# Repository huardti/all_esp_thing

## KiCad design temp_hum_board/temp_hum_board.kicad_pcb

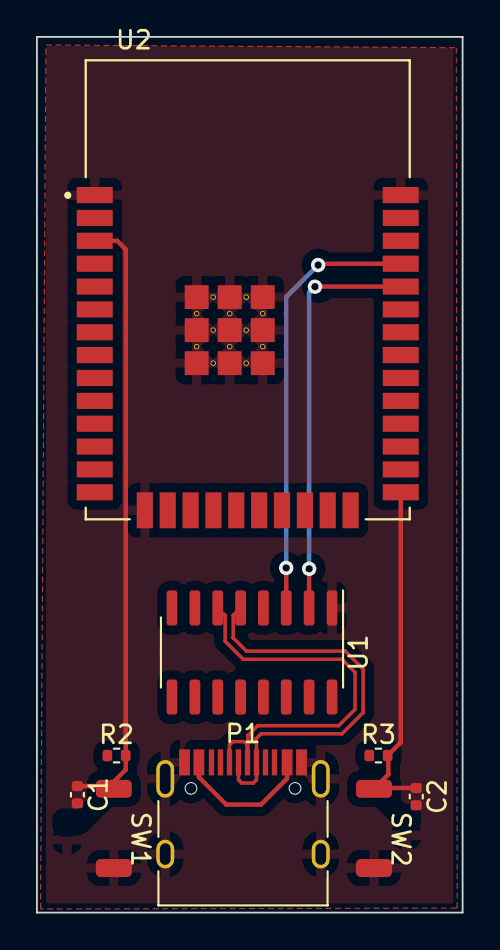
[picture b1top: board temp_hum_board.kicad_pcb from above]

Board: 2 copper layers, 23.6 x 48.7 mm, 9 parts (0 on the bottom side), 9 nets.

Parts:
C1, C2: 0,1µF; C_0402_1005Metric
P1: USB_C_Plug_USB2.0; USB_C_Receptacle_HRO_TYPE-C-31-M-12
R2, R3: 10K; R_0402_1005Metric
SW1, SW2: SW_Push; tactile switch
U1: CH340C; SOIC-16_3.9x9.9mm_P1.27mm
U2: ESP32-WROOM-32E_(4MB); MODULE_ESP32-WROOM-32E_(4MB)

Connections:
+3V3: R2.1, R3.1, U2.2 (3V3)
/D+: P1.A6 (D+), P1.B6 (D+), U1.5 (UD+)
/D-: P1.A7 (D-), P1.B7 (D-), U1.6 (UD-)
EN: C1.1, R2.2, SW1.1, U2.3 (EN)
GND: C1.2, C2.2, P1.A1 (GND), P1.A12 (GND), P1.B1 (GND), P1.B12 (GND), P1.S1 (SHIELD), SW1.2, SW2.2, U1.1 (GND), U2.1 (GND), U2.15 (GND), U2.38 (GND), U2.39_1 (GND), U2.39_2 (GND), U2.39_3 (GND), U2.39_4 (GND), U2.39_5 (GND), U2.39_6 (GND), U2.39_7 (GND), U2.39_8 (GND), U2.39_9 (GND), U2.39_10 (GND), U2.39_11 (GND), U2.39_12 (GND), U2.39_13 (GND), U2.39_14 (GND), U2.39_15 (GND), U2.39_16 (GND), U2.39_17 (GND), U2.39_18 (GND), U2.39_19 (GND), U2.39_20 (GND), U2.39_21 (GND)
IO0: C2.1, R3.2, SW2.1, U2.25 (IO0)
RXD0: U1.2 (TXD), U2.34 (RXD0)
TXD0: U1.3 (RXD), U2.35 (TXD0)
VPP: P1.A4 (VBUS), P1.A9 (VBUS), P1.B4 (VBUS), P1.B9 (VBUS)

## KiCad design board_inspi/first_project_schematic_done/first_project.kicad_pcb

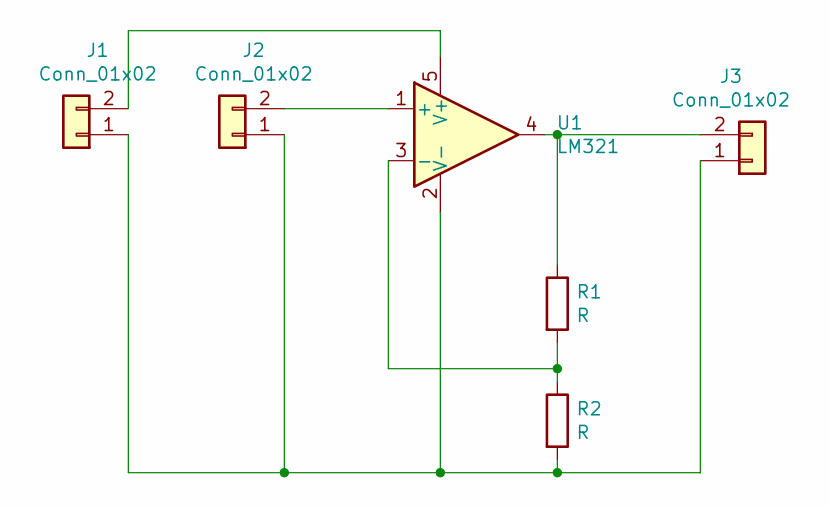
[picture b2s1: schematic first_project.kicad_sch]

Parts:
J1: Conn_01x02; JST_EH_B2B-EH-A_1x02_P2.50mm_Vertical
J2, J3: Conn_01x02; JST_PH_B2B-PH-K_1x02_P2.00mm_Vertical
R1, R2: R; R_0805_2012Metric
U1: LM321; SOT-23-5

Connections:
unnamed: J1.1, J2.1, J3.1, R2.2, U1.2 (V-)
unnamed: J1.2, U1.5 (V+)
unnamed: J2.2, U1.1 (+)
unnamed: J3.2, R1.1, U1.4
unnamed: R1.2, R2.1, U1.3 (-)

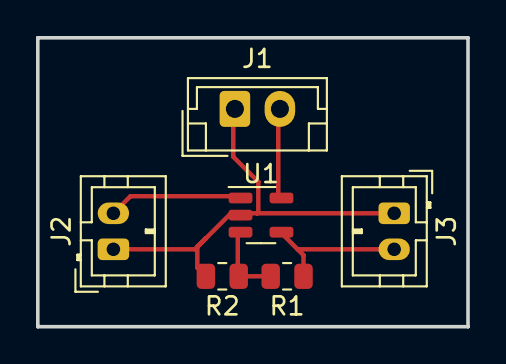
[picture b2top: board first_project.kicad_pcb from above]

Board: 2 copper layers, 23.9 x 16.0 mm, 6 parts (0 on the bottom side), 5 nets.

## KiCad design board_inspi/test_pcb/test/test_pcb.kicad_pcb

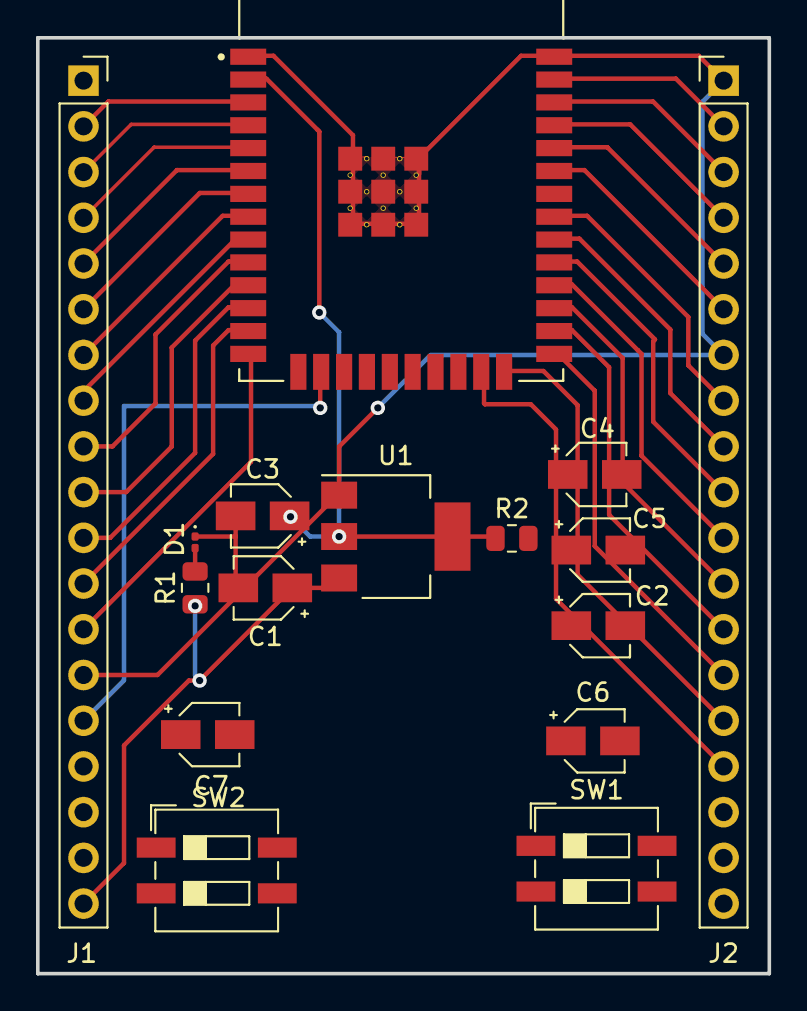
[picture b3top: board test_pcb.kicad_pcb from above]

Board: 2 copper layers, 40.6 x 52.0 mm, 16 parts (0 on the bottom side), 31 nets.

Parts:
C1, C2, C3, C5: 22uF; CP_Elec_3x5.3
C4, C6, C7: 0.1uF; CP_Elec_3x5.3
D1: LED; LED_0201_0603Metric
J1: Conn_01x19; PinSocket_1x19_P2.54mm_Vertical
J2: Conn_01x19; PinHeader_1x19_P2.54mm_Vertical
R1: R; R_0805_2012Metric
R2: 10K; R_0805_2012Metric
SW1, SW2: SW_Push; SW_DIP_SPSTx02_Slide_6.7x6.64mm_W6.73mm_P2.54mm_LowProfile_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
U1: AMS1117-3.3; SOT-223-3_TabPin2
U2: ESP32-WROOM-32E_(4MB); MODULE_ESP32-WROOM-32E_(4MB)

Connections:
/EN: C4.1, C7.2, J1.2, R2.2, SW2.2, U2.3 (EN)
/EXT_5V: C1.1, J1.19, R1.1, U1.3 (VI)
/IO0: C6.2, J2.14, SW1.2, U2.25 (IO0)
/IO2: J2.15, U2.24 (IO2)
/IO4: J2.13, U2.26 (IO4)
/IO5: J2.10, U2.29 (IO5)
/IO12: J1.13, U2.14 (IO12)
/IO13: J1.15, U2.16 (IO13)
/IO14: J1.12, U2.13 (IO14)
/IO15: J2.16, U2.23 (IO15)
/IO16: J2.12, U2.27 (IO16)
/IO17: J2.11, U2.28 (IO17)
/IO18: J2.9, U2.30 (IO18)
/IO19: J2.8, U2.31 (IO19)
/IO21: J2.6, U2.33 (IO21)
/IO22: J2.3, U2.36 (IO22)
/IO23: J2.2, U2.37 (IO23)
/IO25: J1.9, U2.10 (IO25)
/IO26: J1.10, U2.11 (IO26)
/IO27: J1.11, U2.12 (IO27)
/IO32: J1.7, U2.8 (IO32)
/IO33: J1.8, U2.9 (IO33)
/IO34: J1.5, U2.6 (IO34)
/IO35: J1.6, U2.7 (IO35)
/RXD0: J2.5, U2.34 (RXD0)
/SENSOR_VN: J1.4, U2.5 (SENSOR_VN)
/SENSOR_VP: J1.3, U2.4 (SENSOR_VP)
/TXD0: J2.4, U2.35 (TXD0)
/VDD33: C2.1, C3.1, C5.1, R2.1, U1.2 (VO), U2.2 (3V3)
GND: C1.2, C2.2, C3.2, C4.2, C5.2, C6.1, C7.1, D1.1 (K), J1.14, J2.1, J2.7, SW1.1, SW2.1, U1.1 (GND), U2.1 (GND), U2.38 (GND), U2.39_1 (GND), U2.39_2 (GND), U2.39_3 (GND), U2.39_4 (GND), U2.39_5 (GND), U2.39_6 (GND), U2.39_7 (GND), U2.39_8 (GND), U2.39_9 (GND), U2.39_10 (GND), U2.39_11 (GND), U2.39_12 (GND), U2.39_13 (GND), U2.39_14 (GND), U2.39_15 (GND), U2.39_16 (GND), U2.39_17 (GND), U2.39_18 (GND), U2.39_19 (GND), U2.39_20 (GND), U2.39_21 (GND)
unnamed: D1.2 (A), R1.2

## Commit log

2022-03-11 init
2022-03-16 board temp hum
